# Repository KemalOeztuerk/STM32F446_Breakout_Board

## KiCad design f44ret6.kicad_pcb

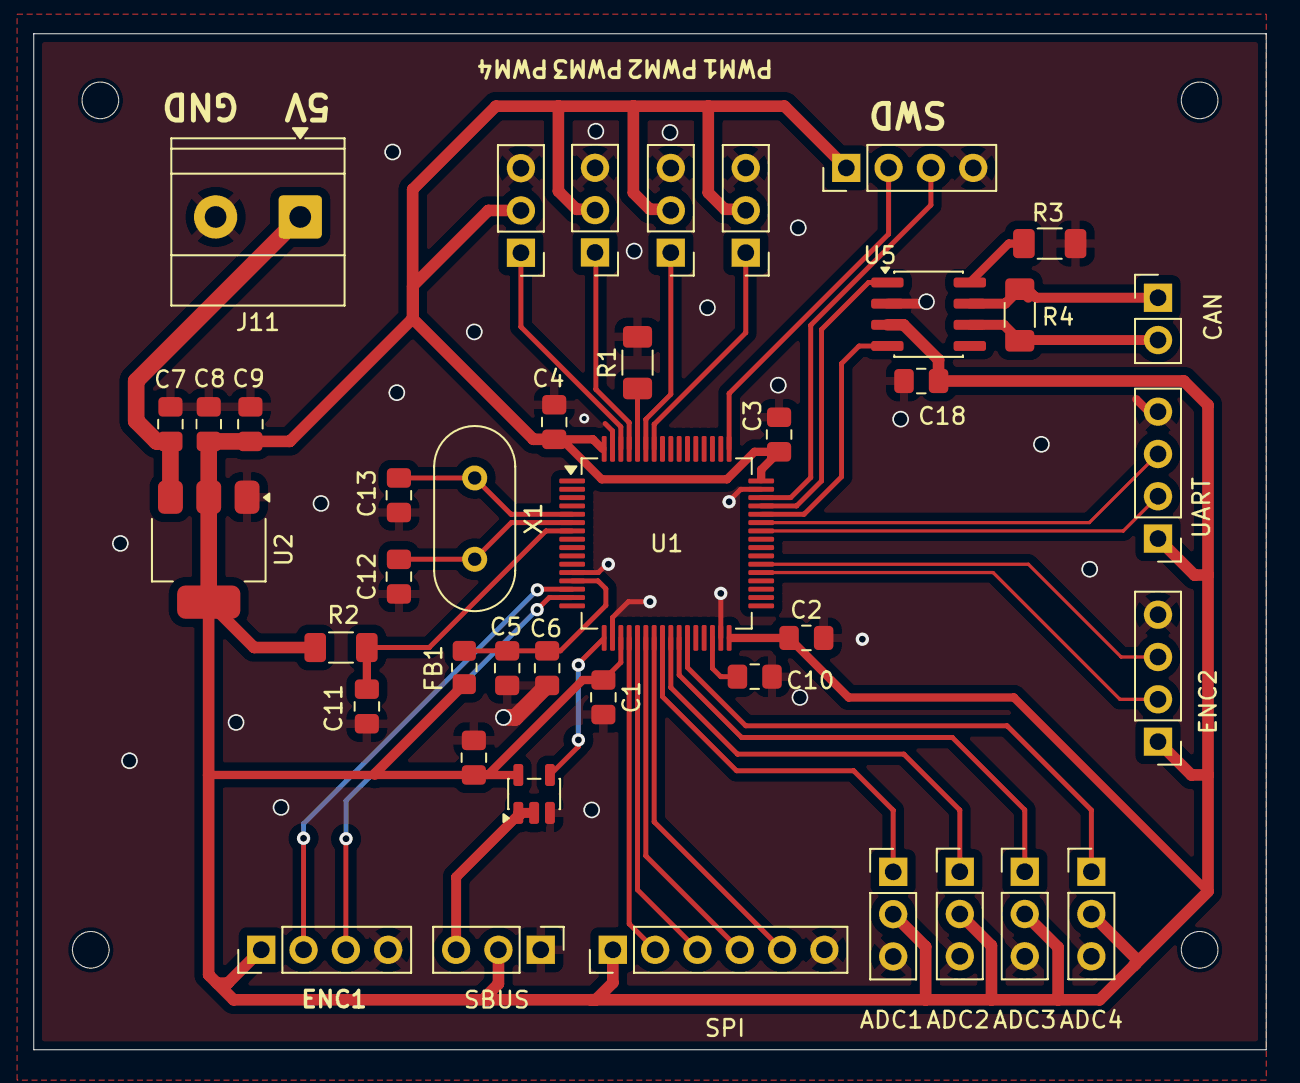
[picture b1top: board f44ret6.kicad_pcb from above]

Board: 2 copper layers, 74.0 x 61.0 mm, 45 parts (0 on the bottom side), 36 nets.

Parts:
ADC1, ADC2, ADC3, ADC4: Conn_01x03; PinHeader_1x03_P2.54mm_Vertical
C1, C2, C3, C4, C11, C17, C18: 100nF; C_0805_2012Metric_Pad1.18x1.45mm_HandSolder
C5: 10nF; C_0805_2012Metric_Pad1.18x1.45mm_HandSolder
C6: 1uF; C_0805_2012Metric_Pad1.18x1.45mm_HandSolder
C7, C8: 10uF; C_0805_2012Metric_Pad1.18x1.45mm_HandSolder
C9, C10: 4.7uF; C_0805_2012Metric_Pad1.18x1.45mm_HandSolder
C12, C13: 22pF; C_0805_2012Metric_Pad1.18x1.45mm_HandSolder
CAN: Conn_01x02; PinHeader_1x02_P2.54mm_Vertical
ENC2: Conn_01x04_Pin; PinHeader_1x04_P2.54mm_Vertical
FB1: 1kR; R_0805_2012Metric_Pad1.20x1.40mm_HandSolder
H1, H2, H3, H4: MountingHole; MountingHole_2.2mm_M2
J1, J8: Conn_01x04_Pin; PinHeader_1x04_P2.54mm_Vertical
J11: Conn_01x02; TerminalBlock_Phoenix_MKDS-1,5-2-5.08_1x02_P5.08mm_Horizont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
J13, J14, J15, J16: Conn_01x03; PinHeader_1x03_P2.54mm_Vertical
R1, R2, R3: 10kΩ; R_1206_3216Metric_Pad1.30x1.75mm_HandSolder
R4: 220Ω; R_1206_3216Metric_Pad1.30x1.75mm_HandSolder
SBUS: Conn_01x03; PinHeader_1x03_P2.54mm_Vertical
SPI: Conn_01x06_Pin; PinHeader_1x06_P2.54mm_Vertical
U1: STM32F446RETx; LQFP-64_10x10mm_P0.5mm
U2: AMS1117-3.3; SOT-223-3_TabPin2
U4: SN74LVC1G00DBV; SOT-23-5
U5: SN65HVD230; SOIC-8_3.9x4.9mm_P1.27mm
UART: Conn_01x04_Pin; PinHeader_1x04_P2.54mm_Vertical
X1: X50328MSB2GI; Crystal_HC49-U_Vertical

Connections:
+3.3VA: C5.1, C6.1, FB1.1, U1.13 (VDDA)
+3V3: ADC1.2, ADC2.2, ADC3.2, ADC4.2, C1.1, C2.1, C3.1, C4.1, C8.1, C9.1, C17.1, C18.2, ENC2.1, FB1.2, J1.1, J8.1, J13.2, J14.2, J15.2, J16.2, R2.2, SBUS.2, SPI.1, U1.19 (VDD), U1.32 (VDD), U1.48 (VDD), U1.64 (VDD), U2.2 (VO), U4.5 (VCC), U5.3 (VCC), UART.1
+5V: C7.1, J11.1, U2.3 (VI)
/ADC2_IN8: ADC3.1, U1.26 (PB0)
/ADC2_IN9: ADC4.1, U1.27 (PB1)
/ADC2_IN14: ADC1.1, U1.24 (PC4)
/ADC2_IN15: ADC2.1, U1.25 (PC5)
/BOOT: R1.1, U1.60 (BOOT0)
/CAN1_RX: U1.44 (PA11), U5.4 (R)
/CAN1_TX: U1.45 (PA12), U5.1 (D)
/CANH: CAN.1, R4.2, U5.7 (CANH)
/CANL: CAN.2, R4.1, U5.6 (CANL)
/ENC1A: J8.2, U1.14 (PA0)
/ENC1B: J8.3, U1.15 (PA1)
/ENC2A: ENC2.2, U1.37 (PC6)
/ENC2B: ENC2.3, U1.38 (PC7)
/NRST: C11.1, R2.1, U1.7 (NRST)
/PWM1: J13.1, U1.58 (PB6)
/PWM2: J14.1, U1.59 (PB7)
/PWM3: J15.1, U1.61 (PB8)
/PWM4: J16.1, U1.62 (PB9)
/RCC_OSC_IN: C13.1, U1.5 (PH0), X1.1
/RCC_OSC_OUT: C12.1, U1.6 (PH1), X1.2
/SBUS: SBUS.3, U4.1, U4.2
/SPI1_CS: SPI.2, U1.20 (PA4)
/SPI1_MISO: SPI.4, U1.22 (PA6)
/SPI1_MOSI: SPI.5, U1.23 (PA7)
/SPI1_SCK: SPI.3, U1.21 (PA5)
/SWCLK: J1.2, U1.49 (PA14)
/SWDIO: J1.3, U1.46 (PA13)
/UART1_RX: U1.43 (PA10), UART.3
/UART1_TX: U1.42 (PA9), UART.2
/UART2_RX: U1.17 (PA3), U4.4
GND: ADC1.3, ADC2.3, ADC3.3, ADC4.3, C1.2, C2.2, C3.2, C4.2, C5.2, C6.2, C7.2, C8.2, C9.2, C10.2, C11.2, C12.2, C13.2, C17.2, C18.1, ENC2.4, J1.4, J8.4, J11.2, J13.3, J14.3, J15.3, J16.3, R1.2, R3.1, SBUS.1, SPI.6, U1.12 (VSSA), U1.18 (VSS), U1.31 (VSS), U1.47 (VSS), U1.63 (VSS), U2.1 (GND), U4.3 (GND), U5.2 (GND), UART.4
unnamed: C10.1, U1.30 (VCAP_1)
unnamed: R3.2, U5.8 (Rs)
